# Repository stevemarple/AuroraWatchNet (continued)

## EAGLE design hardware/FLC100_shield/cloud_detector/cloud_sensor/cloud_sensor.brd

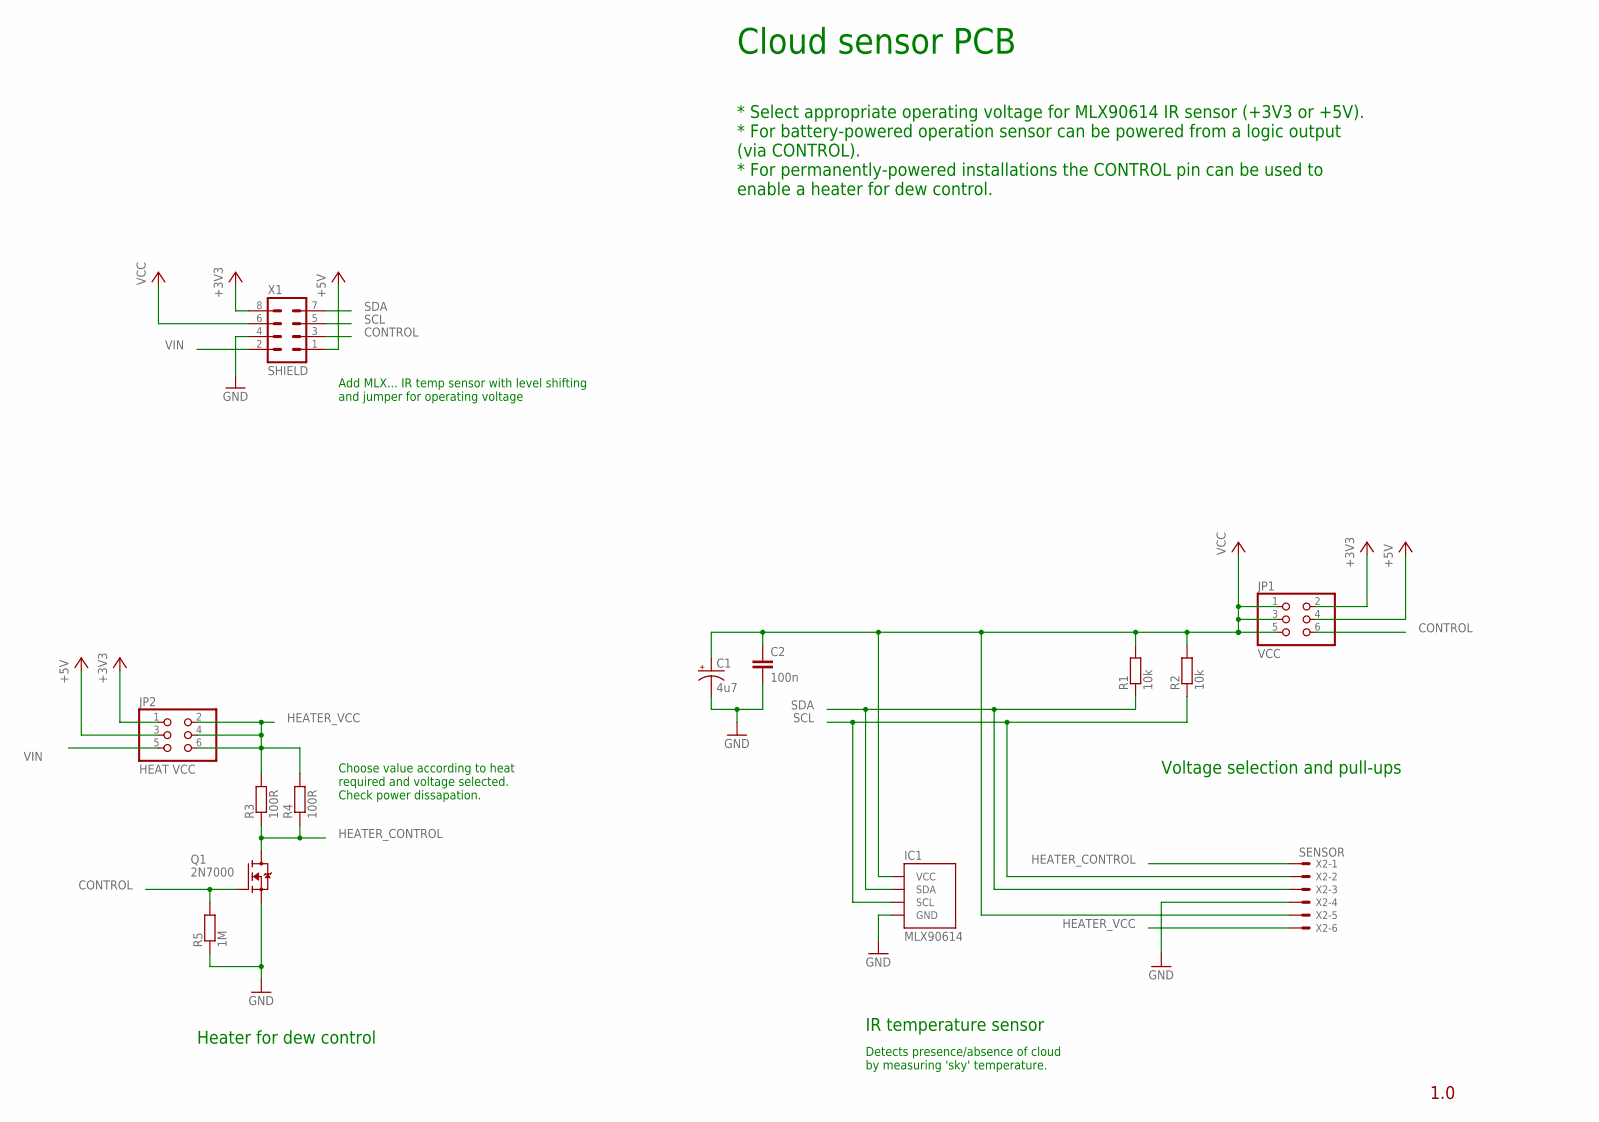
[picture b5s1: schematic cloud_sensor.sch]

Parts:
C1: 4u7; CPOL-RADIAL-10UF-25V
C2: 100n; CAP-PTH-SMALL
IC1: MLX90614; TO39-4
JP1: VCC; 2X03
JP2: HEAT VCC; 2X03
Q1: 2N7000; TO-92
R1, R2: 10k; RES-AXIAL-0.4
R3, R4: 100R; RES-AXIAL-0.4
R5: 1M; RES-AXIAL-0.4
X1: SHIELD; ML8
X2: SENSOR; 22-23-2061

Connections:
+3V3: JP1.2, JP2.1, X1.8
+5V: JP1.4, JP2.3, X1.1
CONTROL: JP1.6, Q1.2 (G), R5.P$2 (2), X1.3
GND: C1.2 (-), C2.2, IC1.4 (GND), Q1.1 (S), R5.P$1 (1), X1.4, X2.4
HEATER_CONTROL: Q1.3 (D), R3.P$1 (1), R4.P$1 (1), X2.1
HEATER_VCC: JP2.2, JP2.4, JP2.6, R3.P$2 (2), R4.P$2 (2), X2.6
SCL: IC1.1 (SCL), R2.P$1 (1), X1.5, X2.2
SDA: IC1.2 (SDA), R1.P$1 (1), X1.7, X2.3
VCC: C1.1 (+), C2.1, IC1.3 (VCC), JP1.1, JP1.3, JP1.5, R1.P$2 (2), R2.P$2 (2), X1.6, X2.5
VIN: JP2.5, X1.2

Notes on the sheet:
Add MLX... IR temp sensor with level shifting and jumper for operating voltage
Choose value according to heat required and voltage selected. Check power dissapation.
IR temperature sensor
Detects presence/absence of cloud by measuring 'sky' temperature.
Cloud sensor PCB
* Select appropriate operating voltage for MLX90614 IR sensor (+3V3 or +5V). * For battery-powered operation sensor can be powered from a logic output (via CONTROL). * For permanently-powered installations the CONTROL pin can be used to enable a heater for dew control.
Voltage selection and pull-ups
Heater for dew control
1.0

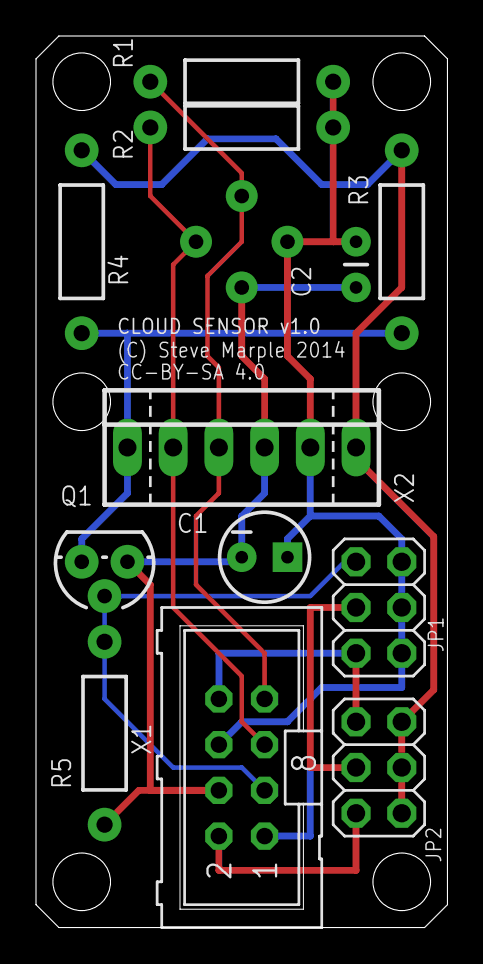
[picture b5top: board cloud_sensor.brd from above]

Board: 2 copper layers, 22.9 x 49.5 mm, 13 parts (1 on the bottom side), 10 nets.

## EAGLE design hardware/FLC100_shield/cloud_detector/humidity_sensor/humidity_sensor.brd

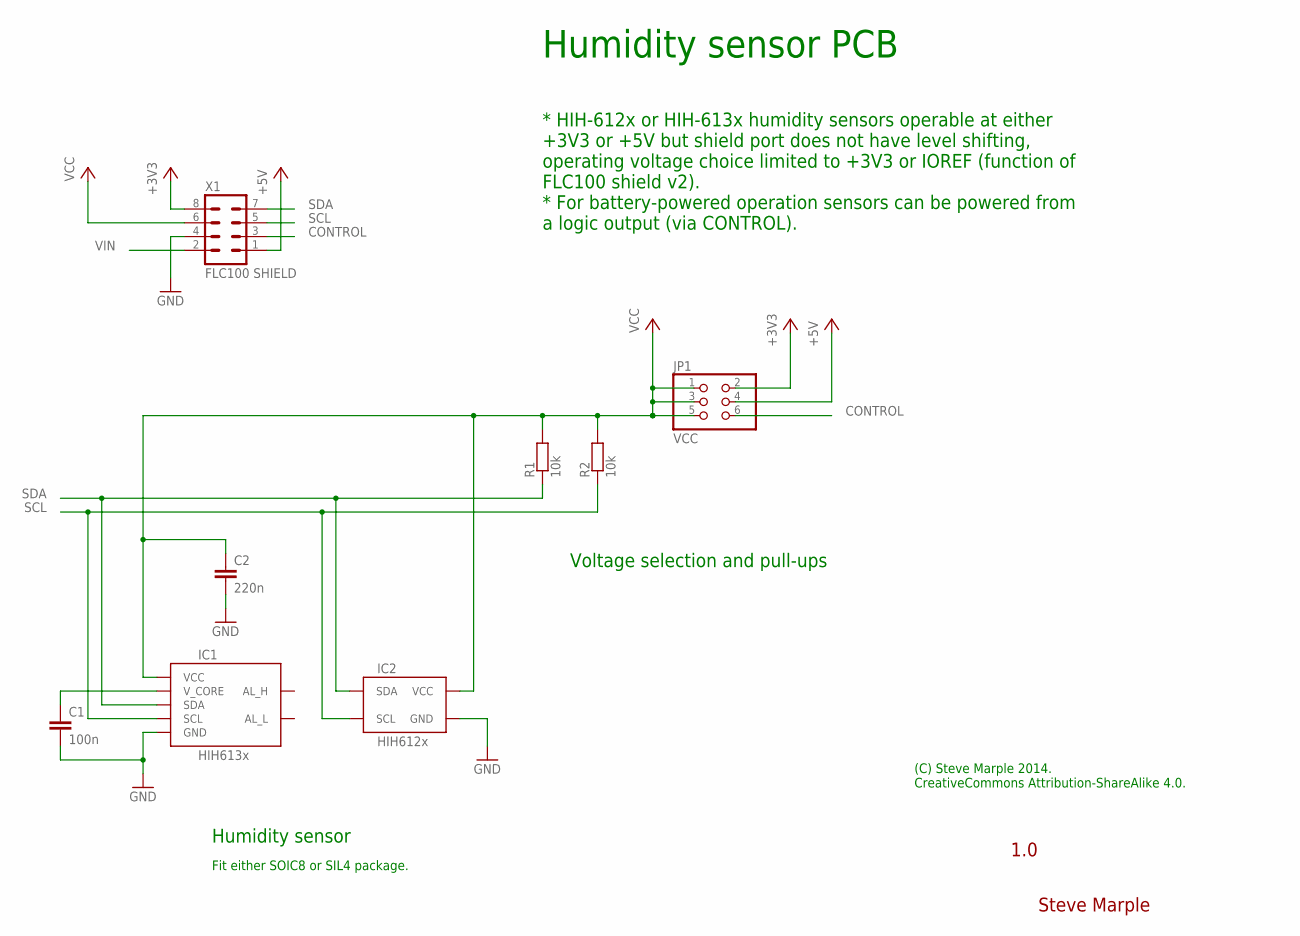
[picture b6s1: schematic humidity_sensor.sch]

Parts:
C1: 100n; CAP-PTH-SMALL
C2: 220n; CAP-PTH-SMALL
IC1: HIH613x; SO08
IC2: HIH612x; SIL04
JP1: VCC; 2X03
R1, R2: 10k; RES-AXIAL-0.4
X1: FLC100 SHIELD; ML8

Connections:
+3V3: JP1.2, X1.8
+5V: JP1.4, X1.1
CONTROL: JP1.6, X1.3
GND: C1.2, C2.2, IC1.2 (GND), IC2.2 (GND), X1.4
unnamed: C1.1, IC1.1 (V_CORE)
SCL: IC1.3 (SCL), IC2.3 (SCL), R2.P$1 (1), X1.5
SDA: IC1.4 (SDA), IC2.4 (SDA), R1.P$1 (1), X1.7
VCC: C2.1, IC1.8 (VCC), IC2.1 (VCC), JP1.1, JP1.3, JP1.5, R1.P$2 (2), R2.P$2 (2), X1.6
VIN: X1.2

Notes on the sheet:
Humidity sensor
Fit either SOIC8 or SIL4 package.
Humidity sensor PCB
* HIH-612x or HIH-613x humidity sensors operable at either +3V3 or +5V but shield port does not have level shifting, operating voltage choice limited to +3V3 or IOREF (function of FLC100 shield v2). * For battery-powered operation sensors can be powered from a logic output (via CONTROL).
Voltage selection and pull-ups
(C) Steve Marple 2014. CreativeCommons Attribution-ShareAlike 4.0.
Steve Marple
1.0

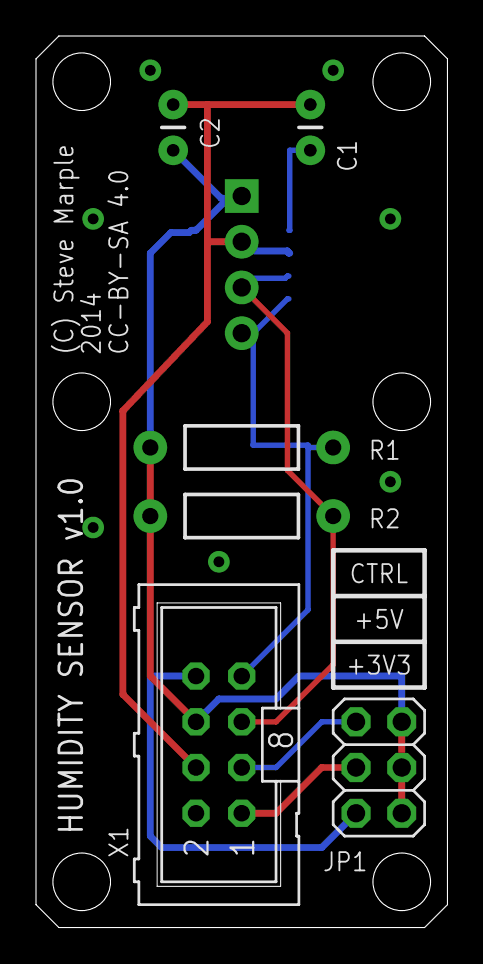
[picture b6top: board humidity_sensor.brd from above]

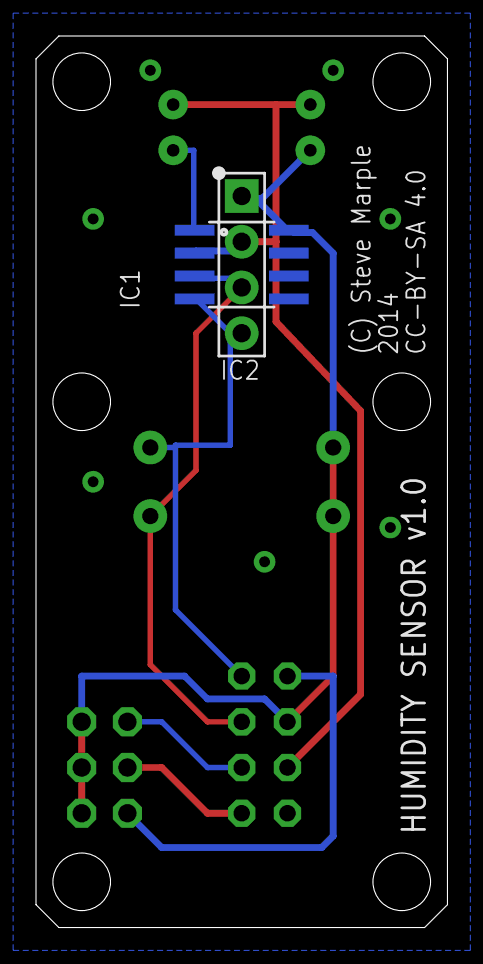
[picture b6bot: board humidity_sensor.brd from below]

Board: 2 copper layers, 22.9 x 49.5 mm, 8 parts (2 on the bottom side), 8 nets.

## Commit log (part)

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2017-07-01 Read CPU temperature only if required
2017-07-01 Read Honeywell HIH6xxx humidity sensors
2017-07-02 Support reading value from a file
    Removes special case for "cpu_temperature". Can read from any file where
    the content is a single value parseable by float(). Optional
    "scale_factor" and "offset" options (similar to MCP342x) allow the
    numeric value to be converted, eg to the appropriate units.
2017-07-02 Log the columns to be recorded
    If the data file already exists the column headers are not writte.
    Ensure the information is always put into the log file in case the
    columns or their ordering changes.
2017-07-10 Update manual for latest Raspbian
    Allow full or `lite` version of Raspbian to be used.
2017-07-12 Read site information from logger daemon config file
    Adds option to read from the logger daemon's config file (typically
    /etc/awnet.ini) to obtain project, site and file path. The file path
    allows auroraplot to use local data files without auroraplot
    customisation.
2017-07-14 Send only sensor temperature
    Changed following discussions with MetOffice and WOW developers that
    only sensor temperature will be imported.
2017-07-19 PEP8 fixes
2017-07-19 Enable file types for upload to be set in config file
    Allows different file types to be uploaded to different hosts.
2017-07-30 Add firmware for MagCloud-0.31a
2017-08-03 Enable rsync options to be adjusted from ini file
2017-08-12 Split manual into 3 versions
    Three versions:
    * The original design using a Calunium microcontroller. Covers
    both radio and PoE versions.
    * The AuroraWatchNet Raspberry Pi magnetometer. Uses a custom
    interface PCB with an ADC for each FLC100 sensor.
    * The BGS Raspberry Pi magnetometer for schools. Uses the AB
2017-08-12 Instructions to contribute data to Met Office WOW
2017-08-22 Update instructions to match displayed text
2017-08-22 Add ntp to package requirements
2017-08-30 Bump version: 0.31b → 0.32a
2017-09-12 Set production URL for WOW uploads
2017-09-30 Bugfix: correct path to image
2017-11-05 Update for Debian/Raspbian 9 (stretch)
    Remove old SSH instructions.
2018-04-20 Document data quality feature
2018-04-20 Ignore netbeans and other IDE project files
2018-04-23 Remove trailing whitespacw
2018-04-23 Add riometer feature
2018-04-24 Add EEPROM settings for riometer logger
2018-04-24 Add support for riometer logger hardware
    Software support based on FLC100 shield software sa the hardware is very
    similar.
2018-04-24 Update library version
2018-04-24 PEP8 and format changes
2018-04-24 Update riometer EEPROM settings
2018-04-24 Fix console output and EEPROM settings
2018-04-24 Improve start up messages
    Clearly identify between DHCP request and remove hostname lookup. Print
    site ID.
2018-04-25 Add script to conveniently generate and format the HMAC key
2018-04-25 Add information about pin usage
2018-04-26 Support ATmega1284 (non-P) microcontroller
2018-04-26 Scanning improvements
2018-04-26 Rename cols -> columns
2018-04-26 Improved debug output for riometer data
2018-04-30 Ensure remote_addr is defined
2018-04-30 Fix Python 2/3 compatiblity to avoid IDE warnings
2018-04-30 Rename decode_tag_payload => format_tag_payload
2018-05-10 Update RTCx to v1.1.0 for PCF85263 support
2018-05-10 Use RTCx v1.1.2
2018-05-11 Fix indenting and clean up whitespace
2018-05-14 Bugfix: fix decoding of flags to correct epoch
2018-05-24 Add support for ATmega1284 (non-P version)
2018-05-24 Don't disable brown-out detection for ATmega1284 (non-P version)
    Code compiled on the ATmega1284P can run on the ATmega1284. The hardware
    doesn't support disabling brown-out detection during sleep mode. Don't
    attempt to disable when ATmega1284 is running ATmega1284P code.
2018-05-24 Add support for ATmega1284 (non-P vdrsion)
2018-05-24 Use "sent" not "received" when printing response message
2018-05-25 Tidy printing
2018-05-25 Use separate CommandHandler library
2018-05-30 Refactor RioLogger to new library style
2018-05-30 Add test program to check board operation
2018-06-03 Add support for HIH61xx, read and print sensor values
2018-06-07 Use sizeof() for actual buffer size
2018-06-07 Indicate if microcontroller is ATMega1284 or ATmega1284P
2018-06-10 Clarify arguments to addMessage()
2018-06-10 Add missing initializations
2018-06-10 Add feature to use an output pin to display sampling duty cycle
2018-06-13 Use 2018-01-01 for the alternative epoch
2018-06-13 Make response timeout public
2018-06-13 Add device signatures and MCU name
2018-06-13 Write log messages to the log file
2018-06-13 Bump version: 0.01a → 0.2a
2018-06-16 Bugfix: add missing tag length sizes
2018-06-16 Refactor startup to send EEPROM settings
2018-06-20 Revise EEPROM settings for riometer
    Add EEPROM settings to configure housekeeping data collection that can
    occur during the settling time of the riometer sampling, giving a
    maximum of 8 different periods to collect housekeeping data.
    Similar configuration is used for the riometer sampling.
2018-06-23 Send riometer data as generic signed 32 bit data
2018-06-23 Decode generalised signed 32 bit data
2018-06-23 Save generic signed 32 bit data
    WIP. Need to separate duplicated tags based on the data ID
2018-06-28 Bugfix: fix unresolved buffer reference
2018-06-28 Reword comment to avoid pycharm flagging an error in the comment
2018-06-28 Handle keyboard interrupt, write to log file
2018-06-28 Send riometer EEPROM configuration
2018-07-01 Take riometer ADC settings from new EEPROM settings
    Use the EEPROM_RIO_RIOMETER_* settings for the ADC configuration,
    following the same format used for housekeeping data.
2018-07-01 Take riometer scan mapping from EEPROM
2018-07-01 Bugfix: Use correct secions to output generic data
2018-08-12 Use AS3935 v1.0.3
2018-09-06 Use alternative to Ethernet library that uses HW watchdog
    Based on the Arduino Ethernet library but inserts calls to kick the
    watchdog if the macro ETHERNETWDT_USE_WDT is defined.
2018-09-06 All builds should use WDT support for W5100 Ethernet
2018-09-13 Remove nodiratime instructions
    nodiratime is implied by noatime
2018-09-13 Use ip instead of ifconfig
    Recent versions of ifconfig break the parsing.
2018-09-13 Compile riometer firmware
2018-09-14 Use common reboot() function everywhere
2018-09-14 Use MicroNMEA v1.0.5
2018-09-19 Change console baud rate, fix type
2018-09-19 Add EEPROM settings for GNSS baud rates
    Allow for a default (power-on) baud rate that initial communication must
    occur at, and for a desired baud rate that will be set for normal
    operation.
2018-09-19 Add getter scan state
2018-09-19 Bugfix: honour EEPROM ADC addresses
    If the EEPROM indicates an address outside the valid range the device
    should be considered as missing.
2018-09-19 Refactor LED timeout
    Move eeprom_read_byte() out of loop() for timing reasons.
2018-09-19 Reset GNSS module before use with hardware reset
2018-09-19 Operate GNSS module at lower baud rate
    Operarate a lower baud rate so that it is easier for the microcontroller
    to service the serial port interrupt routine frequently enough to not
    drop characters.
2018-09-19 Fix version string
2018-09-19 Make default target to compile all firmware
2018-09-23 Add verbosity to standard features
2019-04-22 Configure presample delay from EEPROM setting
2019-06-22 Allow for ADCs that record housekeeping data without riometer data
2019-06-22 EEPROM programming information update
2019-06-22 Add trailing newline
2019-06-30 Add extra patch levels (e-z)
2019-06-30 Add firmware for RioLog v1.1a
2019-06-30 Bump version: 1.1a → 1.1b
2019-06-30 Update custom_include.h with settings for serial buffer sizes
2019-06-30 Add riometer firmware RioLog-1.1c
    Required for serial buffer size changes.
2019-08-07 Remove unwanted IDE files
2020-01-15 Add a "path" option for rsync uploads
    Used only for rsync uploads. For HTTP(S) use the "url" option. For
    rrsync uploads the remote path is assumed to be defined in the SSH
    config file on the remote host.
2020-10-03 Support automatic wired/wireless detection
    If the interface is not specified use the first interface that is up.
    This helps support automatic detection of wired ethernet and WiFi.
2020-10-11 [doc] Correct path
2020-10-11 [MagCloud] Update for templated HIH61xx library
    Library was templated to support Wire and SoftWire interfaces.
2020-10-11 [libraries] Update MLX90614 to v0.1.5
2020-10-11 [libraries] Update CommandHandler to v1.0.0
2020-10-11 Bump version: 1.1c → 1.2a
2020-10-11 Bump version: 1.2a → 1.2b
2020-10-18 [RioLog] Tidy console output
    Prefix I2C hex addresses with 0x instead of Ox.
    Improve description of RTC initialisation.
2020-10-18 Bump version: 1.2b → 1.2c
2020-10-19 [libraries] Update MicroNMEA to v2.0.2
2020-10-24 [RioLog] Print xboot version information on startup
2020-10-24 [RioLog] Fix CPU name when sending log message
2020-10-24 [libraries] Update GNSS_Clock to v0.2.1
    Update to v0.2.1 so that the time in the GNSS messages can be read.
2020-10-24 [server] Improve GNSS logging
    If the GNSS message was from a valid fix then log the GNSS data using
    the GNSS message timestamp. Otherwise use the microntroller's sample
    time for the GNSS message.
2020-10-24 Bump version: 1.2d → 1.2e
2020-12-29 Bump version: 1.2e → 1.2f
2020-12-29 [RioLog] Add firmware for 1.2g
2020-12-29 [RioLog] Add firmware for 1.2h
2021-03-26 Add riometer manual
    Create a version of the manual dedicated to the riometer. Document the
    relevant config file options.
    Update EEPROM settings documentation. There can be considerable overlap
    between the various settings so document all EEPROM settings in all
    versions of the manual to avoid omissions. User will see all settings
    anyway when using the Python script so they should have the
2021-03-28 Add PoE magnetometer hardware design
2024-04-01 [doc] Update manual to insert missing riometer instructions
2024-04-01 [server] Fix minor errors in setup.py
    Fixes for minor errors reported by pycharm.
2024-04-01 [doc] Add instruction to check the firmware path
2024-04-01 [server] Update check_ntp_status to use python3
    Update for Python 3. Fix minor warnings found by pycharm. Fix PEP8 style
    issues.
2024-05-04 [server] Add basic riometer INI file
2024-05-27 [RioLog] MicroNMEA error handlers need non-const reference
    As a result of MicroNMEA change 692e6e72e8f81c9bf8665f6b5f360ad05dc097a8
    the error handlers should take a non-const reference so they can call
    `clear()` if required.
2024-05-27 fixup! [server] Use Python 3
2024-05-27 [RioLog] Update mkfwimage.py for Python 3
2024-05-27 [RioLog] Correct function prototypes
    Function prototypes did not match the definitions.
2024-05-27 [RioLog] Fix unused variable warnings
2024-08-11 [doc] Fix some build problems
    Make the various manuals build independently by removing the
    intermediate latex files.
2024-08-11 Ignore all VS code files
2025-03-09 [server] Update control message handling for Python 3
    Update for Python 3.
    Improve error handling, use logging exceptions to print a stack trace.
    Do not allow multiple concurrent `read_eeprom` or `write_eeprom`
    commands.
    Add a `--clear-pending` option to send_cmd.py that clear all pending
    commands. This is more convenient than restarting the logging daemon.
2025-03-09 Restore Raspberry Pi setup instructions
2025-07-13 Replace python2 str.decode('hex') functionality
    Use `binascii.unhexlify` to replace python2 str.decode('hex')
    functionality.
2025-11-09 SafeConfigParser removed from configparser
    configparser v6.0.0 removed SafeConfigParser, use ConfigParser instead.
2025-11-10 [doc] Document how to configure private network
    When a separate microcontroller is used for data acquisition it must be
    programmed with the IP address or hostname of the Raspberry Pi data
    logger. This can be a problem when the full network details are not
    known before deployment. In such cases it is helpful to install a
    private network between the microcontroller and Raspberry Pi.
2025-12-01 [server] Fix send_cmd for Python 3
2026-03-29 [GitHub] Add workflows to build/release docs
    Requires LaTeX to generate the documentation. Libreoffice is used to
    convert drawings from ODG to PDF.
